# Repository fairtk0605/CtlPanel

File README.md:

# CtlPanel
This project aims to develop a circuit box which controls multiple devices like valve , pump , motor etc.
This box have a touch panel and this touch panel supports graphical contoroll for those devices.

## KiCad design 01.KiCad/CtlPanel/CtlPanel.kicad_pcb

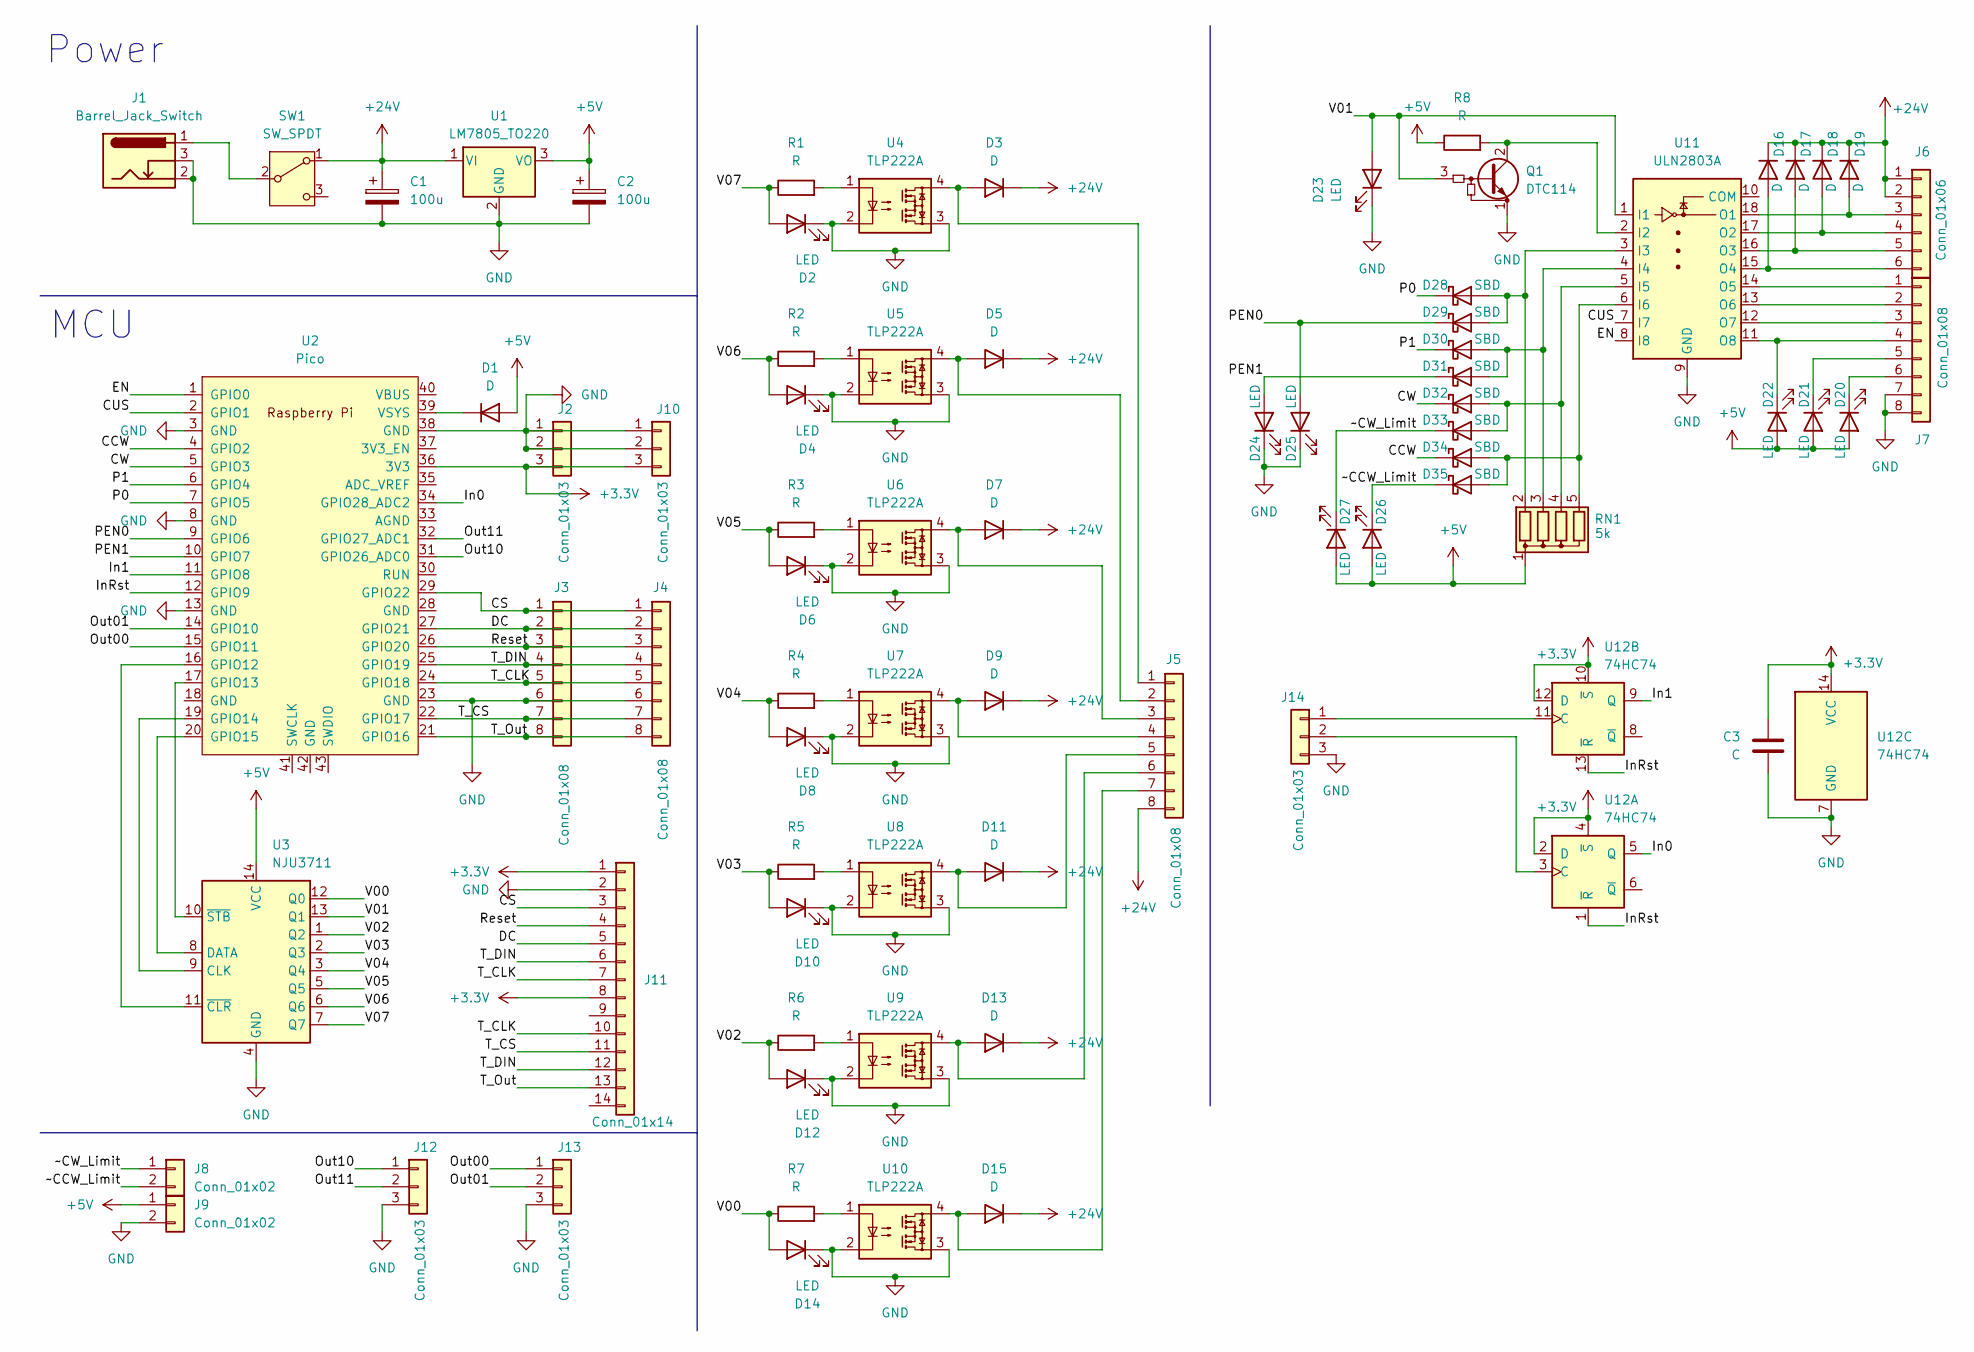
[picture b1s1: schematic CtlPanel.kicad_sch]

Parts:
C1, C2: 100u; CP_Radial_D5.0mm_P2.50mm
C3: C; C_Disc_D3.0mm_W1.6mm_P2.50mm
D1: D; D_DO-34_SOD68_P10.16mm_Horizontal
D2, D4, D6, D8, D10, D12, D14, D20, D21, D22, D23, D24, D25, D26, D27: LED; LED_D3.0mm
D3, D5, D7, D9, D11, D13, D15, D16, D17, D18, D19: D; D_DO-34_SOD68_P2.54mm_Vertical_AnodeUp
D28, D29, D30, D32, D34: SBD; D_DO-34_SOD68_P2.54mm_Vertical_AnodeUp
D31: SBD; D_DO-34_SOD68_P10.16mm_Horizontal
D33: SBD; R_Axial_DIN0207_L6.3mm_D2.5mm_P15.24mm_Horizontal
D35: SBD; R_Axial_DIN0309_L9.0mm_D3.2mm_P12.70mm_Horizontal
J1: Barrel_Jack_Switch; BarrelJack_CUI_PJ-102AH_Horizontal
J2, J10: Conn_01x03; PinHeader_1x03_P2.54mm_Vertical
J3, J4, J5, J7: Conn_01x08; PinHeader_1x08_P2.54mm_Vertical
J6: Conn_01x06; PinHeader_1x06_P2.54mm_Vertical
J8, J9: Conn_01x02; PinHeader_1x02_P2.54mm_Vertical
J11: Conn_01x14; PinHeader_1x14_P2.54mm_Vertical
J12, J13, J14: Conn_01x03; PinHeader_1x03_P2.54mm_Horizontal
Q1: DTC114; TO-92_Wide
R1, R2, R3, R4, R5, R6, R7: R; R_Axial_DIN0204_L3.6mm_D1.6mm_P2.54mm_Vertical
R8: R; R_Axial_DIN0207_L6.3mm_D2.5mm_P17.78mm_Horizontal
RN1: 5k; R_Array_SIP5
SW1: SW_SPDT; PinHeader_1x03_P2.54mm_Vertical
U1: LM7805_TO220; TO-220-3_Vertical
U2: Pico; RPi_Pico_TH
U3: NJU3711; DIP-14_W7.62mm
U4, U5, U6, U7, U8, U9, U10: TLP222A; DIP-4_W7.62mm
U11: ULN2803A; DIP-18_W7.62mm
U12: 74HC74; DIP-14_W7.62mm

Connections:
+3.3V: C3.1, J2.3, J10.3, J11.1, J11.8, U2.36 (3V3), U12.2 (D), U12.4 (~S), U12.10 (~S), U12.12 (D), U12.14 (VCC)
+5V: C2.1, D1.2 (A), D20.2 (A), D21.2 (A), D22.2 (A), D26.2 (A), D27.2 (A), J9.1, R8.1, RN1.1 (common), U1.3 (VO), U3.14 (VCC)
+24V: C1.1, D3.1 (K), D5.1 (K), D7.1 (K), D9.1 (K), D11.1 (K), D13.1 (K), D15.1 (K), D16.1 (K), D17.1 (K), D18.1 (K), D19.1 (K), J5.8, J6.1, J6.2, SW1.1 (A), U1.1 (VI)
/CCW: D34.1 (K), U2.4 (GPIO2)
/CS: J3.1, J4.1, J11.3, U2.29 (GPIO22)
/CUS: U2.2 (GPIO1), U11.7 (I7)
/CW: D32.1 (K), U2.5 (GPIO3)
/DC: J3.2, J4.2, J11.5, U2.27 (GPIO21)
/EN: U2.1 (GPIO0), U11.8 (I8)
/In0: U2.34 (GPIO28_ADC2), U12.5 (Q)
/In1: U2.11 (GPIO8), U12.9 (Q)
/InRst: U2.12 (GPIO9), U12.1 (~R), U12.13 (~R)
/Out00: J13.1, U2.15 (GPIO11)
/Out01: J13.2, U2.14 (GPIO10)
/Out10: J12.1, U2.31 (GPIO26_ADC0)
/Out11: J12.2, U2.32 (GPIO27_ADC1)
/P0: D28.1 (K), U2.7 (GPIO5)
/P1: D30.1 (K), U2.6 (GPIO4)
/PEN0: D25.2 (A), D29.1 (K), U2.9 (GPIO6)
/PEN1: D24.2 (A), D31.1 (K), U2.10 (GPIO7)
/Reset: J3.3, J4.3, J11.4, U2.26 (GPIO20)
/T_CLK: J3.5, J4.5, J11.7, J11.10, U2.24 (GPIO18)
/T_CS: J3.7, J4.7, J11.11, U2.22 (GPIO17)
/T_DIN: J3.4, J4.4, J11.6, J11.12, U2.25 (GPIO19)
/T_Out: J3.8, J4.8, J11.13, U2.21 (GPIO16)
/V00: D14.2 (A), R7.1, U3.12 (Q0)
/V01: D23.2 (A), Q1.3 (B), U3.13 (Q1), U11.1 (I1)
/V02: D12.2 (A), R6.1, U3.1 (Q2)
/V03: D10.2 (A), R5.1, U3.2 (Q3)
/V04: D8.2 (A), R4.1, U3.3 (Q4)
/V05: D6.2 (A), R3.1, U3.5 (Q5)
/V06: D4.2 (A), R2.1, U3.6 (Q6)
/V07: D2.2 (A), R1.1, U3.7 (Q7)
/~CCW_Limit: D26.1 (K), D35.1 (K), J8.2
/~CW_Limit: D27.1 (K), D33.1 (K), J8.1
GND: C1.2, C2.2, C3.2, D2.1 (K), D4.1 (K), D6.1 (K), D8.1 (K), D10.1 (K), D12.1 (K), D14.1 (K), D23.1 (K), D24.1 (K), D25.1 (K), J1.2, J1.3, J2.1, J2.2, J3.6, J4.6, J7.7, J7.8, J9.2, J10.1, J10.2, J11.2, J12.3, J13.3, J14.3, Q1.1 (E), U1.2 (GND), U2.3 (GND), U2.8 (GND), U2.13 (GND), U2.23 (GND), U2.38 (GND), U3.4 (GND), U4.2, U4.3, U5.2, U5.3, U6.2, U6.3, U7.2, U7.3, U8.2, U8.3, U9.2, U9.3, U10.2, U10.3, U11.9 (GND), U12.7 (GND)
unnamed: D1.1 (K), U2.39 (VSYS)
unnamed: D3.2 (A), J5.1, U4.4
unnamed: D5.2 (A), J5.2, U5.4
unnamed: D7.2 (A), J5.3, U6.4
unnamed: D9.2 (A), J5.4, U7.4
unnamed: D11.2 (A), J5.5, U8.4
unnamed: D13.2 (A), J5.6, U9.4
unnamed: D15.2 (A), J5.7, U10.4
unnamed: D16.2 (A), J6.6, U11.15 (O4)
unnamed: D17.2 (A), J6.5, U11.16 (O3)
unnamed: D18.2 (A), J6.4, U11.17 (O2)
unnamed: D19.2 (A), J6.3, U11.18 (O1)
unnamed: D20.1 (K), J7.6
unnamed: D21.1 (K), J7.5
unnamed: D22.1 (K), J7.4, U11.11 (O8)
unnamed: D28.2 (A), D29.2 (A), RN1.2 (R1), U11.3 (I3)
unnamed: D30.2 (A), D31.2 (A), RN1.3 (R2), U11.4 (I4)
unnamed: D32.2 (A), D33.2 (A), RN1.4 (R3), U11.5 (I5)
unnamed: D34.2 (A), D35.2 (A), RN1.5 (R4), U11.6 (I6)
unnamed: J7.1, U11.14 (O5)
unnamed: J7.2, U11.13 (O6)
unnamed: J7.3, U11.12 (O7)
unnamed: J14.1, U12.11 (C)
unnamed: J14.2, U12.3 (C)
unnamed: Q1.2 (C), R8.2, U11.2 (I2)
unnamed: R1.2, U4.1
unnamed: R2.2, U5.1
unnamed: R3.2, U6.1
unnamed: R4.2, U7.1
unnamed: R5.2, U8.1
unnamed: R6.2, U9.1
unnamed: R7.2, U10.1
unnamed: J1.1, SW1.2 (B)
unnamed: U2.16 (GPIO12), U3.11 (~CLR)
unnamed: U2.17 (GPIO13), U3.10 (~STB)
unnamed: U2.19 (GPIO14), U3.9 (CLK)
unnamed: U2.20 (GPIO15), U3.8 (DATA)

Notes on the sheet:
MCU
Power

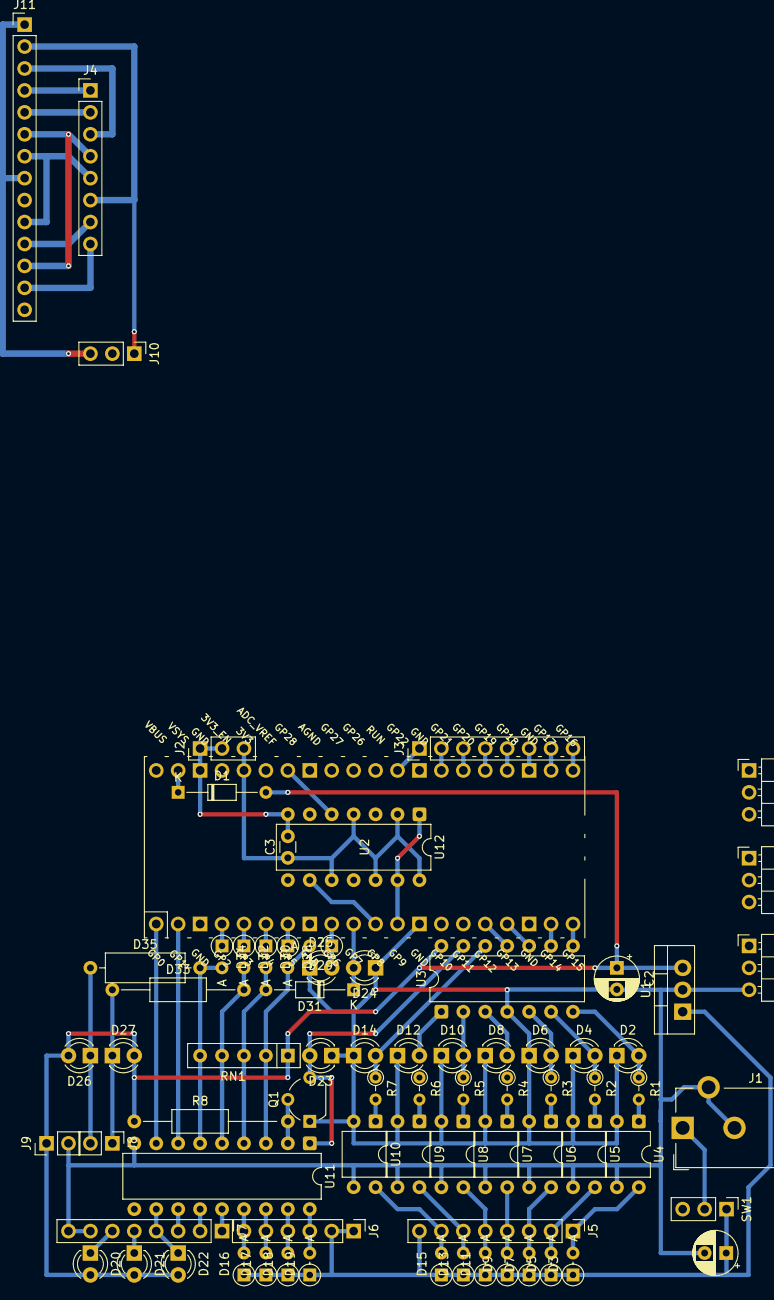
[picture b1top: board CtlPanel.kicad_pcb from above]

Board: 2 copper layers, 75 parts (0 on the bottom side), 73 nets.

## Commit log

2025-04-07 KiCad Done
2025-04-07 Simple README done
2025-04-07 GitIgnore02
2025-04-07 gitignore03
2025-04-07 gitignore04
